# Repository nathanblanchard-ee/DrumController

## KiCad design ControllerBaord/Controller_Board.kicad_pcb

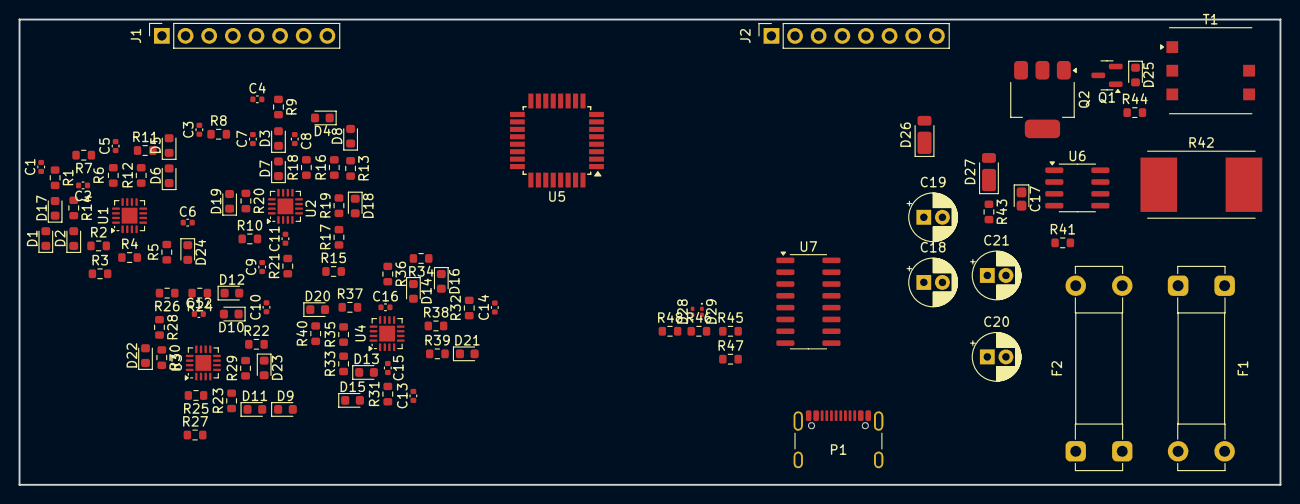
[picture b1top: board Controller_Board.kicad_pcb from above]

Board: 2 copper layers, 135.5 x 50.0 mm, 113 parts (0 on the bottom side), 97 nets, no tracks yet.

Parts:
C1, C3, C9, C13: 100n; C_0402_1005Metric
C2: 330n; C_0402_1005Metric
C4, C5, C6, C7, C8, C10, C11, C12, C14, C15, C16: C; C_0402_1005Metric
C17: C; CP_EIA-1608-08_AVX-J
C18: 1u; CP_Radial_D5.0mm_P2.00mm
C19, C20, C21: C_Polarized; CP_Radial_D5.0mm_P2.00mm
D1, D2, D3, D4, D5, D6, D7, D8, D9, D10, D11, D12, D13, D14, D15, D16, D17, D18, D19, D20, D21, D22, D23, D24, D25: D; D_0603_1608Metric
D26, D27: D; D_PowerDI-123
D28, D29: LED; LED_0201_0603Metric
F1, F2: Fuse; Fuseholder_Clip-5x20mm_Bel_FC-203-22_Lateral_P17.80x5.00mm_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
J1, J2: Conn_01x08; PinSocket_1x08_P2.54mm_Vertical
P1: USB_C_Plug; USB_C_Receptacle_GCT_USB4105-xx-A_16P_TopMnt_Horizontal
Q1: Q_NPN_BCE; SOT-23
Q2: Q_NMOS_DGS; SOT-223
R1, R8, R21, R31: 10k; R_0603_1608Metric
R2: 56k; R_0603_1608Metric
R3: 100k; R_0603_1608Metric
R4: 5.6k; R_0603_1608Metric
R5: 330k; R_0603_1608Metric
R6, R7, R9, R10, R11, R12, R13, R14, R15, R16, R17, R18, R19, R20, R22, R23, R24, R25, R26, R27, R28, R29, R30, R32, R33, R34, R35, R36, R37, R38, R39, R40, R41, R43, R44: R; R_0603_1608Metric
R42: R; R_Shunt_Vishay_WSR2_WSR3
R45, R46, R47, R48: 1k; R_0603_1608Metric
T1: P0544NL; Pulse_PA2002NL-PA2008NL-PA2009NL
U1, U2, U3, U4: LM324; QFN-16-1EP_3x3mm_P0.5mm_EP1.7x1.7mm
U5: ATmega328PB-A; TQFP-32_7x7mm_P0.8mm
U6: MC34063AD; SOIC-8_3.9x4.9mm_P1.27mm
U7: CH340C; SOIC-16_3.9x9.9mm_P1.27mm

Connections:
+5V: C21.1, F1.1, F2.2, P1.A4 (VBUS), P1.A9 (VBUS), P1.B4 (VBUS), P1.B9 (VBUS), R45.2, R46.2, U7.16 (VCC)
+12V: C18.1, C19.1, D26.1 (K), U1.4 (V+), U2.4 (V+), U3.4 (V+), U4.4 (V+)
-12V: C18.2, C19.2, T1.6, U1.11 (V-), U2.11 (V-), U3.11 (V-), U4.11 (V-)
/Signal_Dampner/In1: C1.2, J1.1
/Signal_Dampner/In2: C5.2, J1.2
/Signal_Dampner/In3: C3.2, J1.3
/Signal_Dampner/In4: C4.2, J1.4
/Signal_Dampner/In5: C9.2, J1.5
/Signal_Dampner/In6: C10.2, J1.6
/Signal_Dampner/In7: C13.2, J1.7
/Signal_Dampner/In8: C14.2, J1.8
/Signal_Dampner/Trig_1: D24.1 (K), R5.2, U1.7
/Signal_Dampner/Trig_2: D17.1 (K), R14.2, U1.14
/Signal_Dampner/Trig_3: D18.1 (K), R19.2, U2.7
/Signal_Dampner/Trig_4: D19.1 (K), R20.2, U2.14
/Signal_Dampner/Trig_5: D23.1 (K), R29.2, U3.7
/Signal_Dampner/Trig_6: D22.1 (K), R30.2, U3.14
/Signal_Dampner/Trig_7: D21.1 (K), R39.2, U4.7
/Signal_Dampner/Trig_8: D20.1 (K), R40.2, U4.14
GND: C2.1, C6.1, C7.1, C8.1, C11.1, C12.1, C15.1, C16.1, C20.2, C21.2, J2.1, J2.2, J2.3, J2.4, J2.5, J2.6, J2.7, J2.8, P1.A1 (GND), P1.A12 (GND), P1.B1 (GND), P1.B12 (GND), P1.S1 (SHIELD), Q1.3 (E), Q2.3 (S), R44.1, T1.5, U1.3 (+), U1.5 (+), U1.10 (+), U1.12 (+), U2.3 (+), U2.5 (+), U2.10 (+), U2.12 (+), U3.3 (+), U3.5 (+), U3.10 (+), U3.12 (+), U4.3 (+), U4.5 (+), U4.10 (+), U4.12 (+), U5.5 (GND), U5.21 (GND), U7.1 (GND)
unnamed: C1.1, R1.1
unnamed: C3.1, R8.1
unnamed: C4.1, R9.1
unnamed: C5.1, R11.1
unnamed: C9.1, R21.1
unnamed: C10.1, R22.1
unnamed: C13.1, R31.1
unnamed: C14.1, R32.1
unnamed: C2.2, D1.2 (A), R1.2
unnamed: D1.1 (K), D2.2 (A)
unnamed: D2.1 (K), R2.1
unnamed: C7.2, D3.2 (A), R8.2
unnamed: D3.1 (K), D7.2 (A)
unnamed: C8.2, D4.2 (A), R9.2
unnamed: D4.1 (K), D8.2 (A)
unnamed: C6.2, D5.2 (A), R11.2
unnamed: D5.1 (K), D6.2 (A)
unnamed: D6.1 (K), R12.1
unnamed: D7.1 (K), R10.1
unnamed: D8.1 (K), R13.1
unnamed: C11.2, D9.2 (A), R21.2
unnamed: C12.2, D10.2 (A), R22.2
unnamed: D10.1 (K), D12.2 (A)
unnamed: D9.1 (K), D11.2 (A)
unnamed: D11.1 (K), R23.1
unnamed: D12.1 (K), R24.1
unnamed: C15.2, D13.2 (A), R31.2
unnamed: D13.1 (K), D15.2 (A)
unnamed: C16.2, D14.2 (A), R32.2
unnamed: D14.1 (K), D16.2 (A)
unnamed: D15.1 (K), R33.1
unnamed: D16.1 (K), R34.1
unnamed: D17.2 (A), R7.2, R14.1, U1.13 (-)
unnamed: D18.2 (A), R17.2, R19.1, U2.6 (-)
unnamed: D19.2 (A), R18.2, R20.1, U2.13 (-)
unnamed: D20.2 (A), R38.2, R40.1, U4.13 (-)
unnamed: D22.2 (A), R28.2, R30.1, U3.13 (-)
unnamed: D23.2 (A), R27.2, R29.1, U3.6 (-)
unnamed: D24.2 (A), R4.2, R5.1, U1.6 (-)
unnamed: D25.2 (A), Q1.1 (B), R44.2, U6.2 (SwE)
unnamed: D25.1 (K), Q1.2 (C), Q2.2 (G)
unnamed: D26.2 (A), T1.3
unnamed: D27.2 (A), T1.4
unnamed: D27.1 (K), R43.1
unnamed: D28.2 (A), R45.1
unnamed: D28.1 (K), R48.1, U5.30 (PD0)
unnamed: D29.2 (A), R46.1
unnamed: D29.1 (K), R47.1, U5.31 (PD1)
unnamed: F1.2, R41.1, R42.1
unnamed: P1.A6 (D+), U7.5 (UD+)
unnamed: P1.A7 (D-), U7.6 (UD-)
unnamed: R3.2, R4.1, U1.1
unnamed: R6.2, R7.1, U1.8
unnamed: R15.2, R17.1, U2.1
unnamed: R16.2, R18.1, U2.8
unnamed: R25.2, R27.1, U3.1
unnamed: R26.2, R28.1, U3.8
unnamed: R35.2, R37.1, U4.1
unnamed: R36.2, R38.1, U4.8
unnamed: R42.2, T1.1
unnamed: R2.2, R3.1, U1.2 (-)
unnamed: R6.1, R12.2, U1.9 (-)
unnamed: R10.2, R15.1, U2.2 (-)
unnamed: R13.2, R16.1, U2.9 (-)
unnamed: R23.2, R25.1, U3.2 (-)
unnamed: R24.2, R26.1, U3.9 (-)
unnamed: R33.2, R35.1, U4.2 (-)
unnamed: R37.2, R39.1, U4.6 (-)
unnamed: R34.2, R36.1, U4.9 (-)
unnamed: U5.7 (XTAL1/PB6), U5.8 (XTAL2/PB7), U5.17 (PB5), U5.23 (PC0), U5.24 (PC1), U5.25 (PC2), U5.26 (PC3)
unnamed: C20.1, F2.1, U5.4 (VCC)
unnamed: R41.2, U6.1 (SwC), U6.6 (Vin), U6.7 (Ipk), U6.8 (DC)
unnamed: C17.2, U6.4 (GND)
unnamed: C17.1, U6.3 (TC)
unnamed: R43.2, U6.5 (Vfb)
unnamed: R47.2, U7.3 (RXD)
unnamed: R48.2, U7.2 (TXD)

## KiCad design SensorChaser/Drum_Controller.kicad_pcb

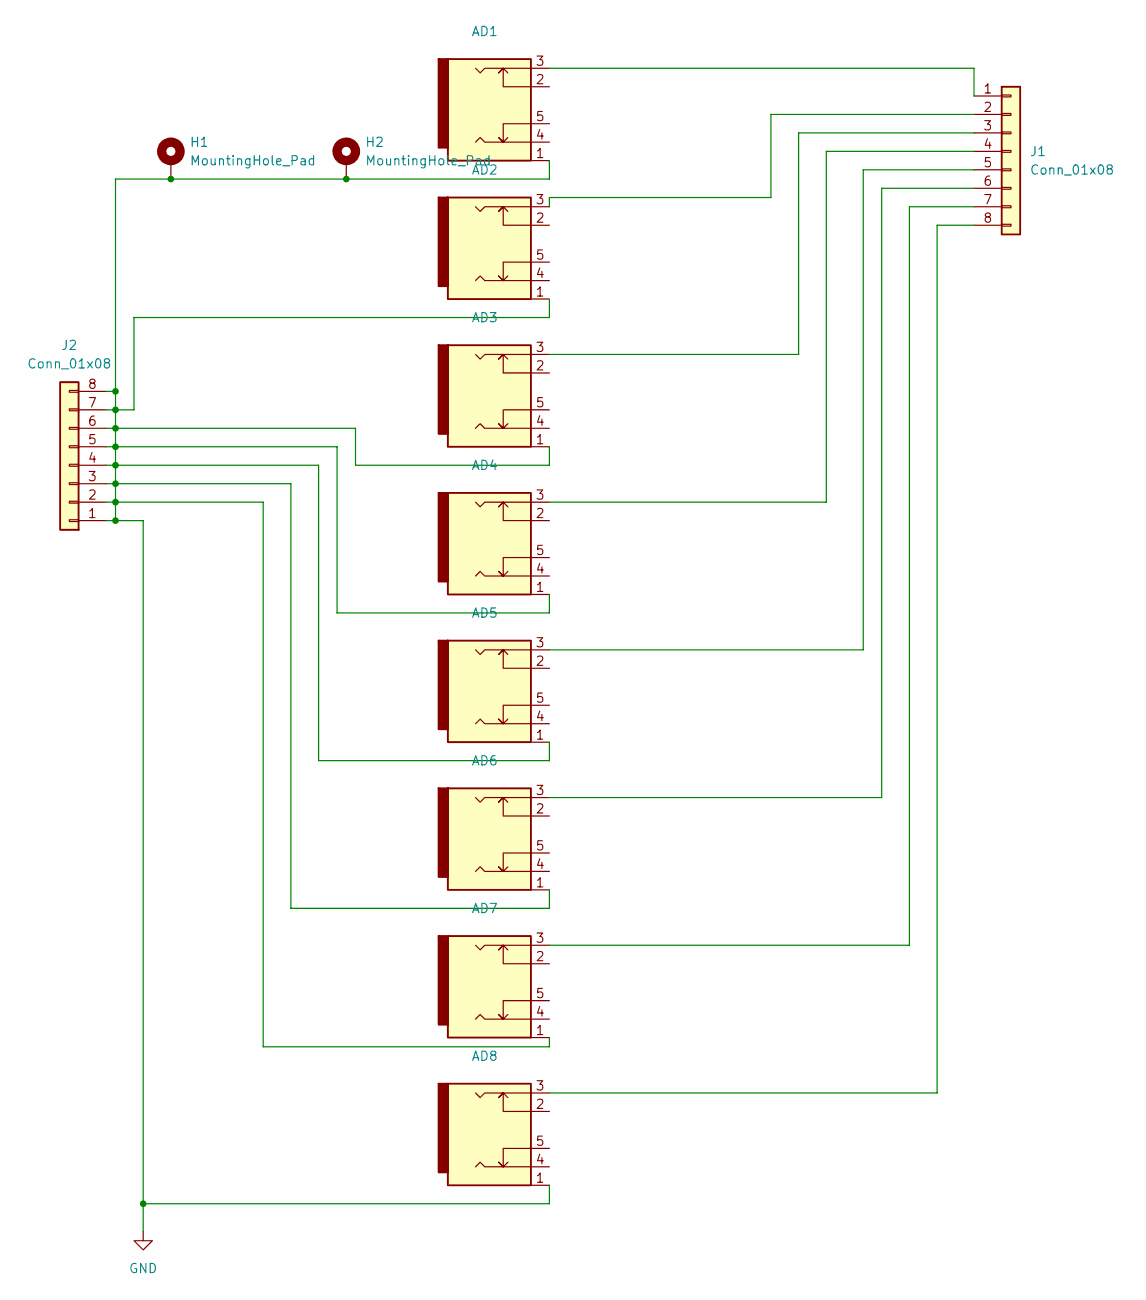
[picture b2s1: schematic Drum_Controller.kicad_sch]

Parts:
AD1, AD2, AD3, AD4, AD5, AD6, AD7, AD8: CK635117
H1, H2: MountingHole_Pad; MountingHole_3.2mm_M3_Pad
J1, J2: Conn_01x08; PinHeader_1x08_P2.54mm_Horizontal

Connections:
GND: AD1.1, AD2.1, AD3.1, AD4.1, AD5.1, AD6.1, AD7.1, AD8.1, H1.1, H2.1, J2.1, J2.2, J2.3, J2.4, J2.5, J2.6, J2.7, J2.8
unnamed: AD1.3, J1.1
unnamed: AD2.3, J1.2
unnamed: AD3.3, J1.3
unnamed: AD4.3, J1.4
unnamed: AD5.3, J1.5
unnamed: AD6.3, J1.6
unnamed: AD7.3, J1.7
unnamed: AD8.3, J1.8

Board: 2 copper layers, 12 parts (0 on the bottom side), 9 nets, no tracks yet.

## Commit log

2025-09-10 Creating folder
2025-09-10 Add signal capture board
    Captures signals from 1/4 inch audio jacks and breaks the signal out into a pin header that can be hooked up to an oscilloscope for signal analysis.
2025-09-10 Adding KiCAD files
2025-09-10 Create ControllerBoard folder
2025-09-10 Add KiCAD files
2025-09-10 Add initial files
2025-09-10 Add arduino code file
